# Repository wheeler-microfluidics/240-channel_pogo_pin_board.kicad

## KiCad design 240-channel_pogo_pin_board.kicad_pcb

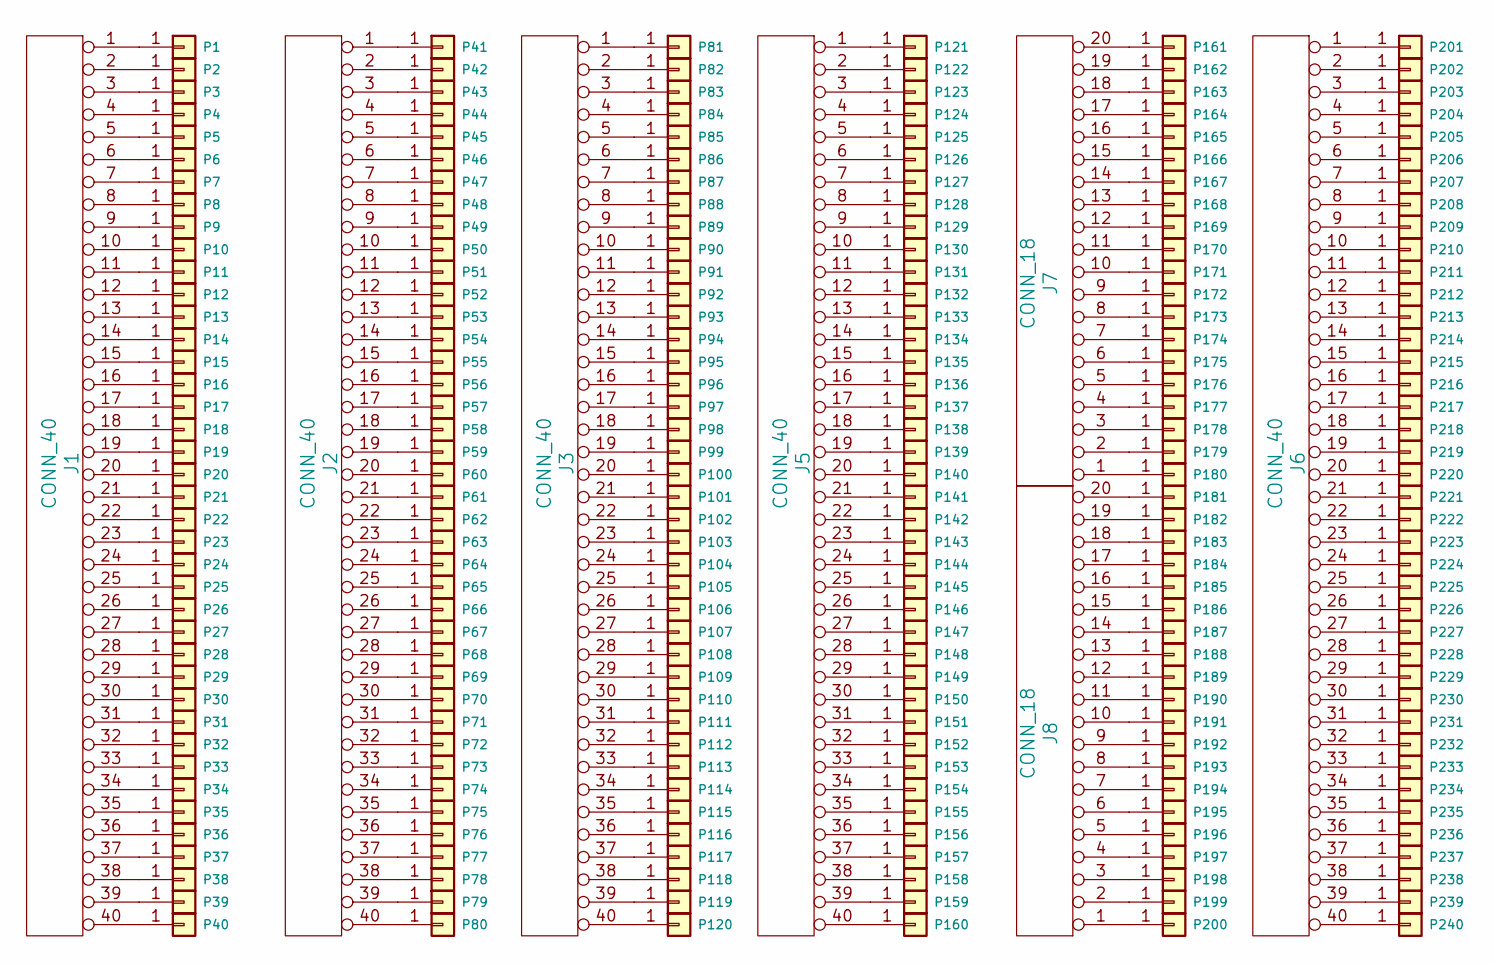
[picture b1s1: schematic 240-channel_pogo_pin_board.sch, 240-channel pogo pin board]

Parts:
J1, J2, J3, J5, J6: CONN_40; TFML-120-01-XXX-D-RA
J7, J8: CONN_18; TFML-110-01-XXX-D-RA
P1, P2, P3, P4, P5, P6, P7, P8, P9, P10, P11, P12, P13, P14, P15, P16, P17, P18, P19, P20, P21, P22, P23, P24, P25, P26, P27, P28, P29, P30, P31, P32, P33, P34, P35, P36, P37, P38, P39, P40, P41, P42, P43, P44, P45, P46, P47, P48, P49, P50, P51, P52, P53, P54, P55, P56, P57, P58, P59, P60, P61, P62, P63, P64, P65, P66, P67, P68, P69, P70, P71, P72, P73, P74, P75, P76, P77, P78, P79, P80, P81, P82, P83, P84, P85, P86, P87, P88, P89, P90, P91, P92, P93, P94, P95, P96, P97, P98, P99, P100, P101, P102, P103, P104, P105, P106, P107, P108, P109, P110, P111, P112, P113, P114, P115, P116, P117, P118, P119, P120, P121, P122, P123, P124, P125, P126, P127, P128, P129, P130, P131, P132, P133, P134, P135, P136, P137, P138, P139, P140, P141, P142, P143, P144, P145, P146, P147, P148, P149, P150, P151, P152, P153, P154, P155, P156, P157, P158, P159, P160, P161, P162, P163, P164, P165, P166, P167, P168, P169, P170, P171, P172, P173, P174, P175, P176, P177, P178, P179, P180, P181, P182, P183, P184, P185, P186, P187, P188, P189, P190, P191, P192, P193, P194, P195, P196, P197, P198, P199, P200, P201, P202, P203, P204, P205, P206, P207, P208, P209, P210, P211, P212, P213, P214, P215, P216, P217, P218, P219, P220, P221, P222, P223, P224, P225, P226, P227, P228, P229, P230, P231, P232, P233, P234, P235, P236, P237, P238, P239, P240: CONN_01X01; pogo_pin

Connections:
unnamed: J1.1, P1.1
unnamed: J1.2, P2.1
unnamed: J1.3, P3.1
unnamed: J1.4, P4.1
unnamed: J1.5, P5.1
unnamed: J1.6, P6.1
unnamed: J1.7, P7.1
unnamed: J1.8, P8.1
unnamed: J1.9, P9.1
unnamed: J1.10, P10.1
unnamed: J1.11, P11.1
unnamed: J1.12, P12.1
unnamed: J1.13, P13.1
unnamed: J1.14, P14.1
unnamed: J1.15, P15.1
unnamed: J1.16, P16.1
unnamed: J1.17, P17.1
unnamed: J1.18, P18.1
unnamed: J1.19, P19.1
unnamed: J1.20, P20.1
unnamed: J1.21, P21.1
unnamed: J1.22, P22.1
unnamed: J1.23, P23.1
unnamed: J1.24, P24.1
unnamed: J1.25, P25.1
unnamed: J1.26, P26.1
unnamed: J1.27, P27.1
unnamed: J1.28, P28.1
unnamed: J1.29, P29.1
unnamed: J1.30, P30.1
unnamed: J1.31, P31.1
unnamed: J1.32, P32.1
unnamed: J1.33, P33.1
unnamed: J1.34, P34.1
unnamed: J1.35, P35.1
unnamed: J1.36, P36.1
unnamed: J1.37, P37.1
unnamed: J1.38, P38.1
unnamed: J1.39, P39.1
unnamed: J1.40, P40.1
unnamed: J2.1, P41.1
unnamed: J2.2, P42.1
unnamed: J2.3, P43.1
unnamed: J2.4, P44.1
unnamed: J2.5, P45.1
unnamed: J2.6, P46.1
unnamed: J2.7, P47.1
unnamed: J2.8, P48.1
unnamed: J2.9, P49.1
unnamed: J2.10, P50.1
unnamed: J2.11, P51.1
unnamed: J2.12, P52.1
unnamed: J2.13, P53.1
unnamed: J2.14, P54.1
unnamed: J2.15, P55.1
unnamed: J2.16, P56.1
unnamed: J2.17, P57.1
unnamed: J2.18, P58.1
unnamed: J2.19, P59.1
unnamed: J2.20, P60.1
unnamed: J2.21, P61.1
unnamed: J2.22, P62.1
unnamed: J2.23, P63.1
unnamed: J2.24, P64.1
unnamed: J2.25, P65.1
unnamed: J2.26, P66.1
unnamed: J2.27, P67.1
unnamed: J2.28, P68.1
unnamed: J2.29, P69.1
unnamed: J2.30, P70.1
unnamed: J2.31, P71.1
unnamed: J2.32, P72.1
unnamed: J2.33, P73.1
unnamed: J2.34, P74.1
unnamed: J2.35, P75.1
unnamed: J2.36, P76.1
unnamed: J2.37, P77.1
unnamed: J2.38, P78.1
unnamed: J2.39, P79.1
unnamed: J2.40, P80.1
unnamed: J3.1, P81.1
unnamed: J3.2, P82.1
unnamed: J3.3, P83.1
unnamed: J3.4, P84.1
unnamed: J3.5, P85.1
unnamed: J3.6, P86.1
unnamed: J3.7, P87.1
unnamed: J3.8, P88.1
unnamed: J3.9, P89.1
unnamed: J3.10, P90.1
unnamed: J3.11, P91.1
unnamed: J3.12, P92.1
unnamed: J3.13, P93.1
unnamed: J3.14, P94.1
unnamed: J3.15, P95.1
unnamed: J3.16, P96.1
unnamed: J3.17, P97.1
unnamed: J3.18, P98.1
unnamed: J3.19, P99.1
unnamed: J3.20, P100.1
unnamed: J3.21, P101.1
unnamed: J3.22, P102.1
unnamed: J3.23, P103.1
unnamed: J3.24, P104.1
unnamed: J3.25, P105.1
unnamed: J3.26, P106.1
unnamed: J3.27, P107.1
unnamed: J3.28, P108.1
unnamed: J3.29, P109.1
unnamed: J3.30, P110.1
unnamed: J3.31, P111.1
unnamed: J3.32, P112.1
unnamed: J3.33, P113.1
unnamed: J3.34, P114.1
unnamed: J3.35, P115.1
unnamed: J3.36, P116.1
unnamed: J3.37, P117.1
unnamed: J3.38, P118.1
unnamed: J3.39, P119.1
unnamed: J3.40, P120.1
unnamed: J5.1, P121.1
unnamed: J5.2, P122.1
unnamed: J5.3, P123.1
unnamed: J5.4, P124.1
unnamed: J5.5, P125.1
unnamed: J5.6, P126.1
unnamed: J5.7, P127.1
unnamed: J5.8, P128.1
unnamed: J5.9, P129.1
unnamed: J5.10, P130.1
unnamed: J5.11, P131.1
unnamed: J5.12, P132.1
unnamed: J5.13, P133.1
unnamed: J5.14, P134.1
unnamed: J5.15, P135.1
unnamed: J5.16, P136.1
unnamed: J5.17, P137.1
unnamed: J5.18, P138.1
unnamed: J5.19, P139.1
unnamed: J5.20, P140.1
unnamed: J5.21, P141.1
unnamed: J5.22, P142.1
unnamed: J5.23, P143.1
unnamed: J5.24, P144.1
unnamed: J5.25, P145.1
unnamed: J5.26, P146.1
unnamed: J5.27, P147.1
unnamed: J5.28, P148.1
unnamed: J5.29, P149.1
unnamed: J5.30, P150.1
unnamed: J5.31, P151.1
unnamed: J5.32, P152.1
unnamed: J5.33, P153.1
unnamed: J5.34, P154.1
unnamed: J5.35, P155.1
unnamed: J5.36, P156.1
unnamed: J5.37, P157.1
unnamed: J5.38, P158.1
unnamed: J5.39, P159.1
unnamed: J5.40, P160.1
unnamed: J6.1, P201.1
unnamed: J6.2, P202.1
unnamed: J6.3, P203.1
unnamed: J6.4, P204.1
unnamed: J6.5, P205.1
unnamed: J6.6, P206.1
unnamed: J6.7, P207.1
unnamed: J6.8, P208.1
unnamed: J6.9, P209.1
unnamed: J6.10, P210.1
unnamed: J6.11, P211.1
unnamed: J6.12, P212.1
unnamed: J6.13, P213.1
unnamed: J6.14, P214.1
unnamed: J6.15, P215.1
unnamed: J6.16, P216.1
unnamed: J6.17, P217.1
unnamed: J6.18, P218.1
unnamed: J6.19, P219.1
unnamed: J6.20, P220.1
unnamed: J6.21, P221.1
unnamed: J6.22, P222.1
unnamed: J6.23, P223.1
unnamed: J6.24, P224.1
unnamed: J6.25, P225.1
unnamed: J6.26, P226.1
unnamed: J6.27, P227.1
unnamed: J6.28, P228.1
unnamed: J6.29, P229.1
unnamed: J6.30, P230.1
unnamed: J6.31, P231.1
unnamed: J6.32, P232.1
unnamed: J6.33, P233.1
unnamed: J6.34, P234.1
unnamed: J6.35, P235.1
unnamed: J6.36, P236.1
unnamed: J6.37, P237.1
unnamed: J6.38, P238.1
unnamed: J6.39, P239.1
unnamed: J6.40, P240.1
unnamed: J7.1, P180.1
unnamed: J7.2, P179.1
unnamed: J7.3, P178.1
unnamed: J7.4, P177.1
unnamed: J7.5, P176.1
unnamed: J7.6, P175.1
unnamed: J7.7, P174.1
unnamed: J7.8, P173.1
unnamed: J7.9, P172.1
unnamed: J7.10, P171.1
unnamed: J7.11, P170.1
unnamed: J7.12, P169.1
unnamed: J7.13, P168.1
unnamed: J7.14, P167.1
unnamed: J7.15, P166.1
unnamed: J7.16, P165.1
unnamed: J7.17, P164.1
unnamed: J7.18, P163.1
unnamed: J7.19, P162.1
unnamed: J7.20, P161.1
unnamed: J8.1, P200.1
unnamed: J8.2, P199.1
unnamed: J8.3, P198.1
unnamed: J8.4, P197.1
unnamed: J8.5, P196.1
unnamed: J8.6, P195.1
unnamed: J8.7, P194.1
unnamed: J8.8, P193.1
unnamed: J8.9, P192.1
unnamed: J8.10, P191.1
unnamed: J8.11, P190.1
unnamed: J8.12, P189.1
unnamed: J8.13, P188.1
unnamed: J8.14, P187.1
unnamed: J8.15, P186.1
unnamed: J8.16, P185.1
unnamed: J8.17, P184.1
unnamed: J8.18, P183.1
unnamed: J8.19, P182.1
unnamed: J8.20, P181.1

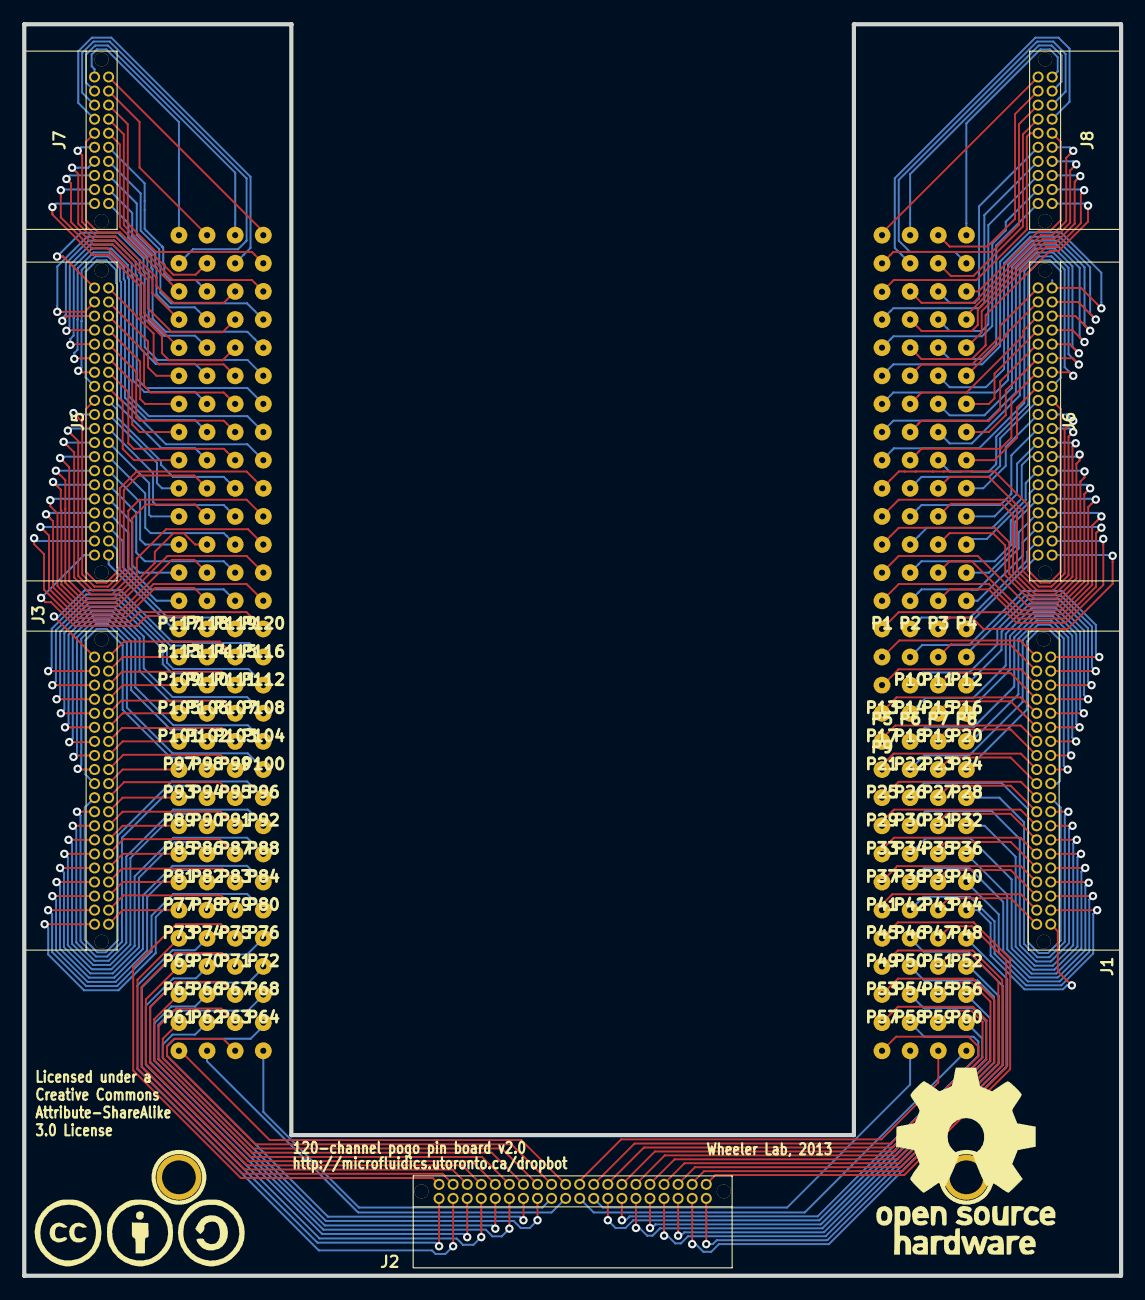
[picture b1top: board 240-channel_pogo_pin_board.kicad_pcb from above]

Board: 2 copper layers, 99.1 x 113.0 mm, 249 parts (0 on the bottom side), 240 nets.

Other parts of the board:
H3: H3; 1pin
H4: H4; 1pin

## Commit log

2019-02-04 240-channel pogo pin board based on 120-channel design.
2019-02-04 add .gitignore

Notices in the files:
240-channel_pogo_pin_board.kicad_pcb:
Licensed under a
Creative Commons
Attribute-ShareAlike
